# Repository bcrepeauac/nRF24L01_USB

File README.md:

# nRF24L01_USB
nRF24L01 adapter board for a computer.

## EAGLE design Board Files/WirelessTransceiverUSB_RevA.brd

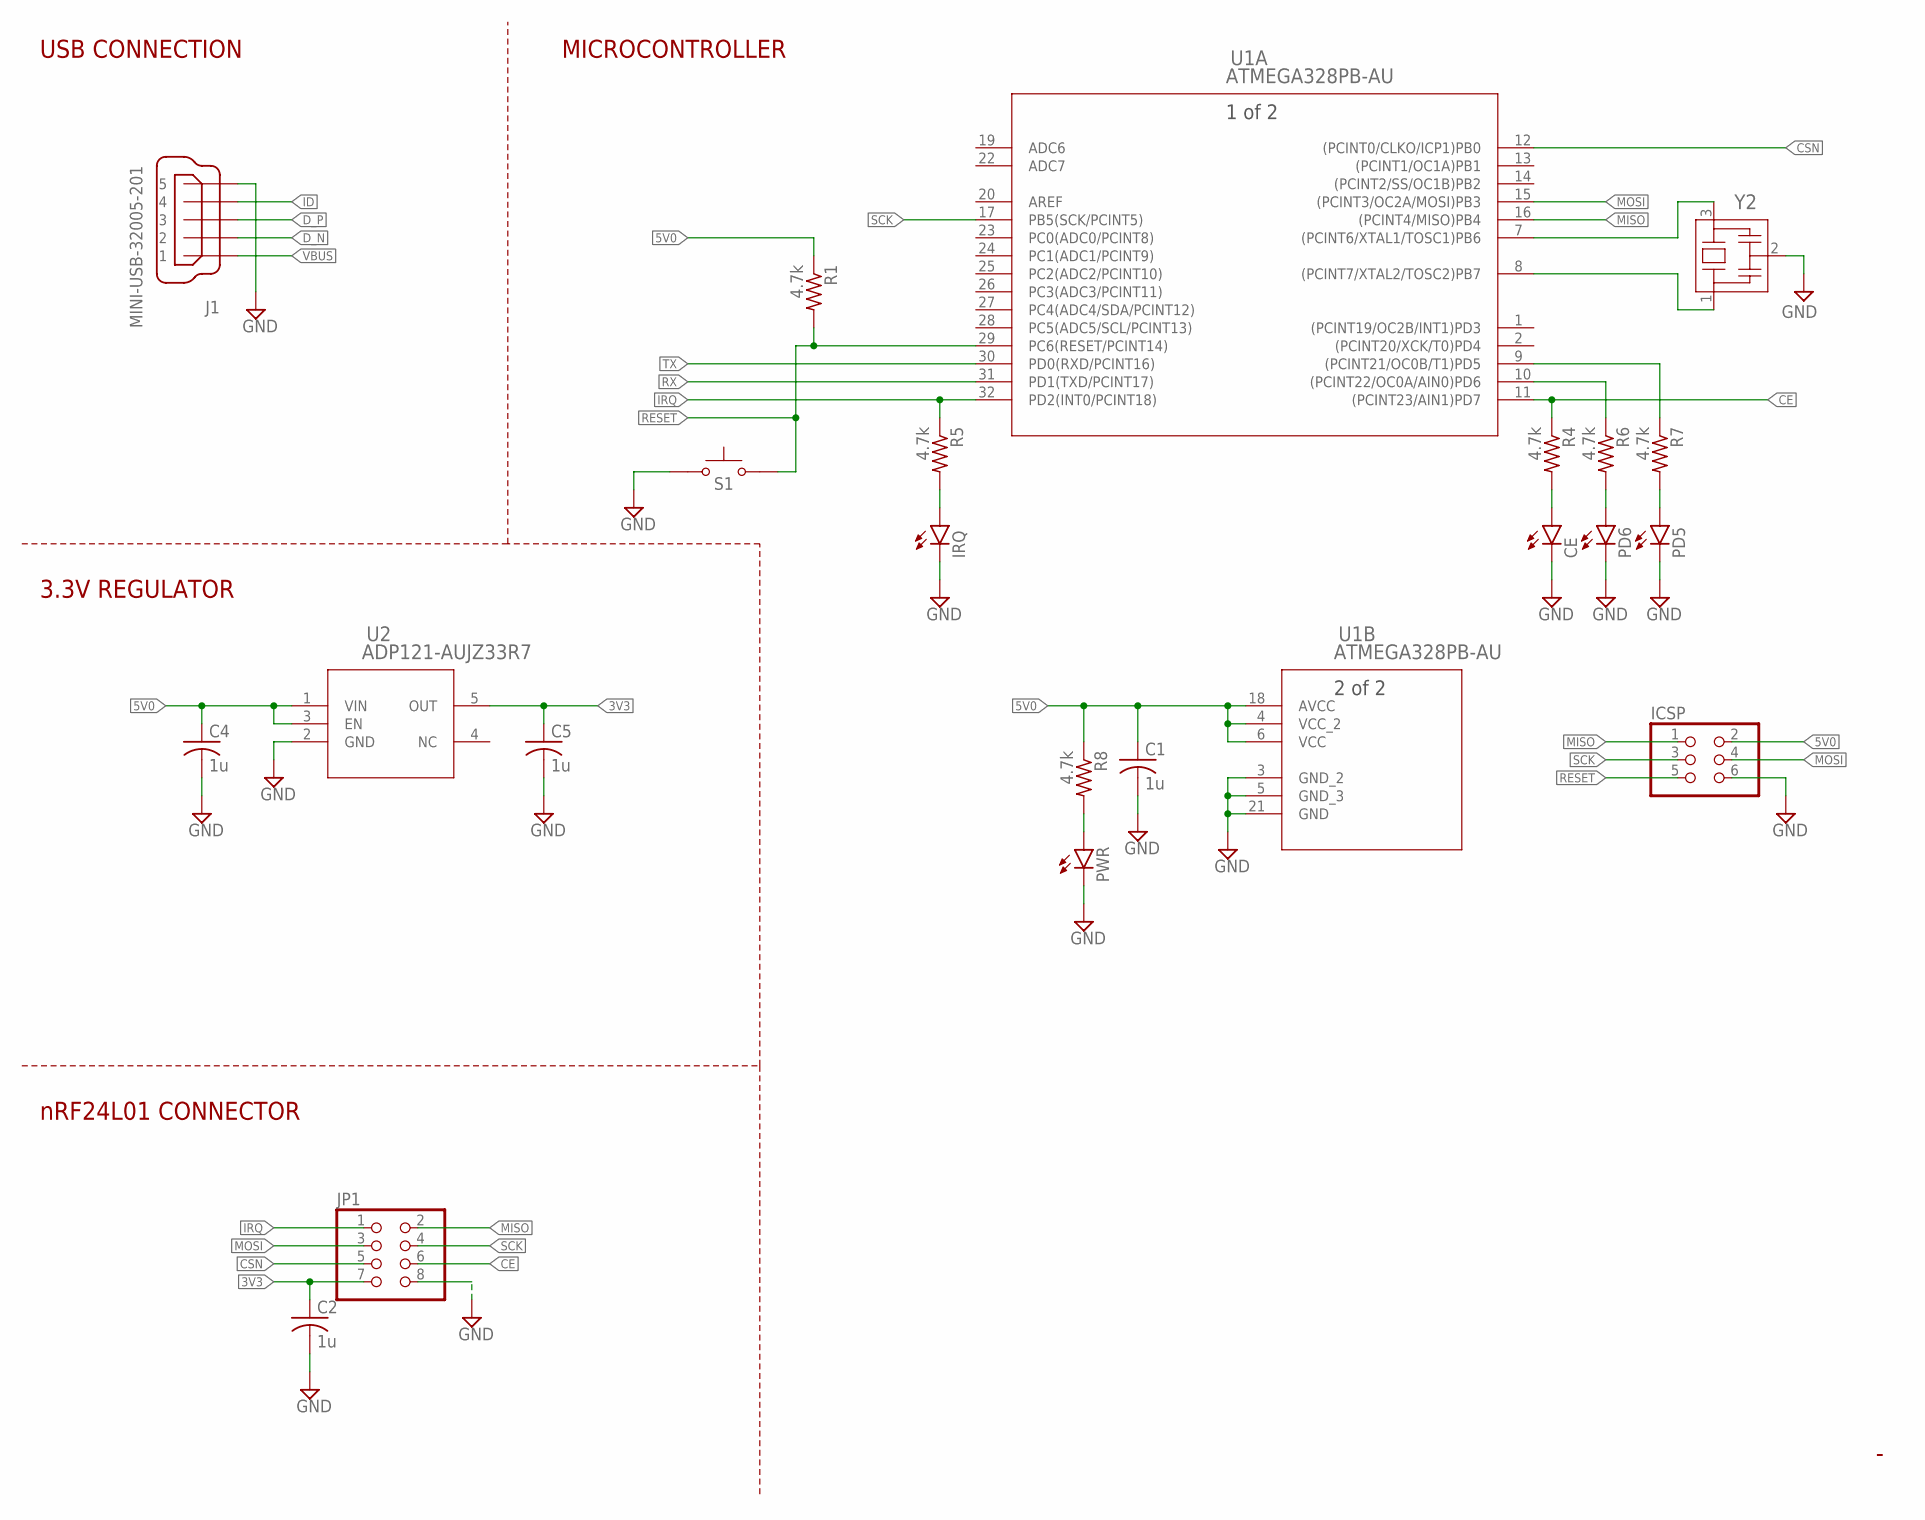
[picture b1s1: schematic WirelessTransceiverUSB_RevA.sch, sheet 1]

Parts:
C1, C2, C4, C5: 1u; C0805
CE: LEDSML0805; SML0805
ICSP: PINHD-2X3; 2X03
IRQ: LEDSML0805; SML0805
J1: MINI-USB-32005-201; 32005-201
JP1: PINHD-2X4; 2X04
PD5, PD6: LEDSML0805; SML0805
PWR: LEDSML0805; SML0805
R1, R4, R5, R6, R7, R8: 4.7k; R0805
S1: TL3315NF100Q; SW_TL3315NF100Q
U1: ATMEGA328PB-AU; 32A_MCH
U2: ADP121-AUJZ33R7; UJ_5_ADI
Y2: CSTNE16M0V530000R0; CSTNE16M0V530000R0_MUR

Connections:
3V3: C2.1, C5.1, JP1.7, U2.5 (OUT); also elsewhere on the board
5V0: C1.1, C4.1, ICSP.2, R1.1, R8.1, U1.4 (VCC_2), U1.6 (VCC), U1.18 (AVCC), U2.1 (VIN), U2.3 (EN); also elsewhere on the board
CE: JP1.6, R4.1, U1.11 ((PCINT23/AIN1)PD7)
CSN: JP1.5, U1.12 ((PCINT0/CLKO/ICP1)PB0)
D_N: J1.2; also elsewhere on the board
D_P: J1.3; also elsewhere on the board
GND: C1.2, C2.2, C4.2, C5.2, CE.C, ICSP.6, IRQ.C, J1.5, JP1.8, PD5.C, PD6.C, PWR.C, S1.1, S1.2 (1), U1.3 (GND_2), U1.5 (GND_3), U1.21 (GND), U2.2 (GND), Y2.2; also elsewhere on the board
ID: J1.4
IRQ: JP1.1, R5.1, U1.32 (PD2(INT0/PCINT18))
MISO: ICSP.1, JP1.2, U1.16 ((PCINT4/MISO)PB4)
MOSI: ICSP.4, JP1.3, U1.15 ((PCINT3/OC2A/MOSI)PB3)
unnamed: U1.7 ((PCINT6/XTAL1/TOSC1)PB6), Y2.3
unnamed: U1.8 ((PCINT7/XTAL2/TOSC2)PB7), Y2.1
unnamed: CE.A, R4.2
unnamed: IRQ.A, R5.2
unnamed: PD5.A, R7.2
unnamed: PD6.A, R6.2
unnamed: PWR.A, R8.2
PD5: R7.1, U1.9 ((PCINT21/OC0B/T1)PD5)
PD6: R6.1, U1.10 ((PCINT22/OC0A/AIN0)PD6)
RESET: ICSP.5, R1.2, S1.3, S1.4 (3), U1.29 (PC6(RESET/PCINT14))
RX: U1.31 (PD1(TXD/PCINT17)); also elsewhere on the board
SCK: ICSP.3, JP1.4, U1.17 (PB5(SCK/PCINT5))
TX: U1.30 (PD0(RXD/PCINT16)); also elsewhere on the board
VBUS: J1.1; also elsewhere on the board

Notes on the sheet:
USB CONNECTION
3.3V REGULATOR
nRF24L01 CONNECTOR
MICROCONTROLLER

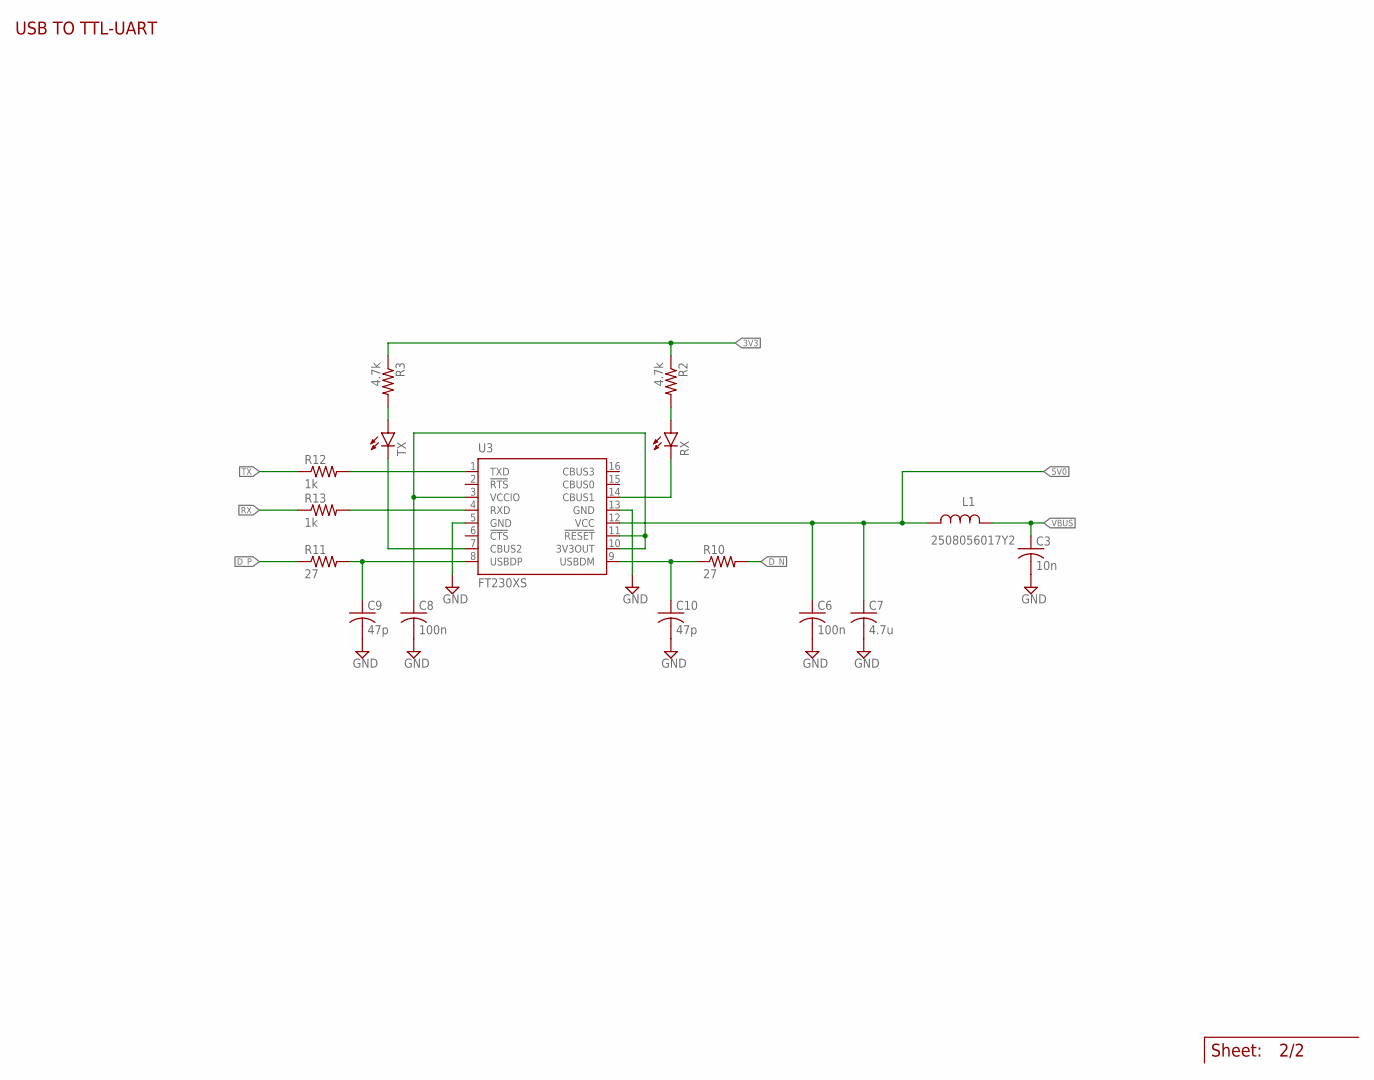
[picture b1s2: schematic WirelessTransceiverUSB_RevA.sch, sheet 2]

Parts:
C3: 10n; C0805
C6, C8: 100n; C0805
C7: 4.7u; C0805
C9, C10: 47p; C0603
L1: 2508056017Y2; IND_25_0805_FRT
R2, R3: 4.7k; R0805
R10, R11: 27; R0603
R12, R13: 1k; R0805
RX: LEDSML0805; SML0805
TX: LEDSML0805; SML0805
U3: FT230XS; SSOP16

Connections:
3V3: R2.1, R3.1; also elsewhere on the board
5V0: C6.1, C7.1, L1.2, U3.12 (VCC); also elsewhere on the board
D_N: R10.2; also elsewhere on the board
D_P: R11.1; also elsewhere on the board
GND: C3.2, C6.2, C7.2, C8.2, C9.2, C10.2, U3.5 (GND), U3.13 (GND); also elsewhere on the board
unnamed: R2.2, RX.A
unnamed: R3.2, TX.A
unnamed: C8.1, U3.3 (VCCIO), U3.10 (3V3OUT), U3.11 (!RESET)
unnamed: TX.C, U3.7 (CBUS2)
unnamed: RX.C, U3.14 (CBUS1)
unnamed: R12.2, U3.1 (TXD)
unnamed: R13.2, U3.4 (RXD)
RX: R13.1; also elsewhere on the board
TX: R12.1; also elsewhere on the board
USBD_N: C10.1, R10.1, U3.9 (USBDM)
USBD_P: C9.1, R11.2, U3.8 (USBDP)
VBUS: C3.1, L1.1; also elsewhere on the board

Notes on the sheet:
Sheet:
USB TO TTL-UART

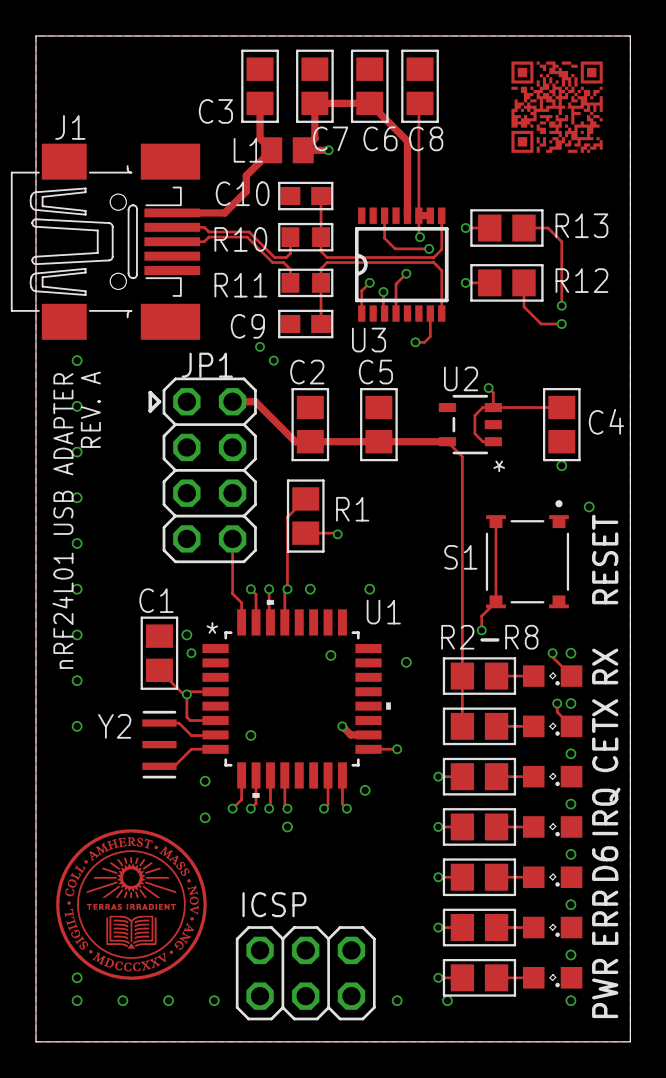
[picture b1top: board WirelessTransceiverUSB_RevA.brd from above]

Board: 4 copper layers, 33.0 x 55.9 mm, 38 parts (0 on the bottom side), 33 nets.

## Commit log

2023-06-14 Corrected .brd file
2023-07-06 Updated to Rev A
    Corrected TX/RX error in board layout and added reset button.

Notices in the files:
parts and their libraries:
COPYRIGHT: Copyright (C) 2023 Ultra Librarian. All rights reserved.
